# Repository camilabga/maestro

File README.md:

# Repository made to support the project Maestro
 
## Introduction
The project consists in a system designed to teach and correct the movement of a blind student that aims to learn a movement. With a OpenCV algorithm and a wearable, we made it possible to these students have a better perception to wheather they are making the gesture correctly or not.

The correction of the movement is passed to the user with an haptic feedback in real time while he/she is executing the gesture.

This work proposes a human gesture evaluation with visual detection and haptic feedback as an additional tool. The purpose is to utilize gesture monitoring with a visual detection alongside markers to execute a gesture following and then, send a haptic feedback to the user.

The project evolved to a different direction. To filter the gesture, we use a machine learning algorithm. At first, a SOM neural network was tested, but then the problem fitted better with a network called [GWR](https://www.sciencedirect.com/science/article/pii/S0893608002000783).

## Installing the requisites
* OpenCV 3.4.x [Installation Guide](https://docs.opencv.org/master/d7/d9f/tutorial_linux_install.html)
* ArUco 3.0.10 [Installation Guide](http://maztories.blogspot.com/2013/07/installing-aruco-augmented-reality.html)

This project was initially executed on a Linux environment with the distribution Ubuntu 16.04. The OpenCV version was 3.4.1 and the ArUco version was 3.0.10. The machine had an Intel Core i5 7th generation and 8GB of RAM Memory.

## Configuring the Wearable

1. Regular motors activation
2. Alternated motors activation

### Regular motors activation
to do

### Alternated motors activation
to do 

## Running the code
The main code is in the ../structure directory. To execute it you must, first choose the mode of execution by editing the **main.cpp** file and the project that contains the NN algorithm (GWR).

It has 4 modes:
1. Recording a new Gesture
2. Running the data through the GWR
3. Running the correction algorithm without the Wearable
4. Running the correction algorithm with the Wearable

### Recording a new Gesture
Open the file **main.cpp** and edit it to look like this:

```c++
Vision vision(argc, argv);
    Trajectory trajectory("../data/square.csv");
    
    trajectory.unnormalize(Point(FRAME_WIDTH/2, FRAME_HEIGHT/2));

    trajectory.saveMovement("../data/new_movement.csv");
    vision.record("../../Videos/random_test.avi");

    while(1){
        vision.calculateTagCenter();
        if (vision.isTargetOn()) {
            trajectory.savePoint(vision.getCenter());
            vision.saveVideo();
        }

        vision.show();
        vision.saveVideo();
    }

    trajectory.endSaving();
```

### Running the data through the GWR
to do

### Running the correction algorithm without the Wearable
Open the file **main.cpp** and edit it to look like this:

```c++
    Vision vision(argc, argv);
    Trajectory trajectory("../data/square.csv");
    trajectory.unnormalize(Point(FRAME_WIDTH/2, FRAME_HEIGHT/2));
    trajectory.saveMovement("../data/random_test.csv");

    while(1){
        vision.calculateTagCenter();
        vision.drawTrajectory(trajectory, trajectory.getCurrentPointId());
        if (vision.isTargetOn()) {
            trajectory.setNextPoint0(vision.getCenter());
            vision.drawError(vision.getCenter(), trajectory.getCurrentPoint());
            trajectory.savePoint(vision.getCenter());
        }

        vision.show();
    }

    trajectory.endSaving();
```

### Running the correction algorithm with the Wearable
Open the file **main.cpp** and edit it to look like this:

```c++
    Vision vision(argc, argv);
    Weareable weareable;
    Trajectory trajectory("../data/square.csv");

    trajectory.unnormalize(Point(FRAME_WIDTH/2, FRAME_HEIGHT/2));
    trajectory.saveMovement("../data/random_test.csv");

    weareable.setIP((char*)"10.6.4.107");
    weareable.start();

    while(1){
        vision.calculateTagCenter();
        vision.drawTrajectory(trajectory, trajectory.getCurrentPointId());
        if (vision.isTargetOn()) {
            trajectory.setNextPoint0(vision.getCenter());
            vision.drawError(vision.getCenter(), trajectory.getCurrentPoint());

            weareable.send(trajectory.getError(vision.getCenter()));

            trajectory.savePoint(vision.getCenter());
        }

        vision.show();
    }

    trajectory.endSaving();
```

## Article(s) Published
### Human Gesture Evaluation with Visual Detection and Haptic Feedback
**Abstract:** Learning a gesture pertains to learning a expression of motion by a human, involving the hands, arms, face, head, and/or body. In this work, we propose to employ haptic feedback as an additional tool in the gesture following/evaluation loop. Accordingly, the user wears a haptic wearable device in the form of a bracelet which vibrates according to the trajectory error. Our research hypothesis is then to investigate whether such haptic device aids the user in correcting his movement in relation to the prerecorded trajectory.

**Acess in:** https://dl.acm.org/citation.cfm?id=3243104

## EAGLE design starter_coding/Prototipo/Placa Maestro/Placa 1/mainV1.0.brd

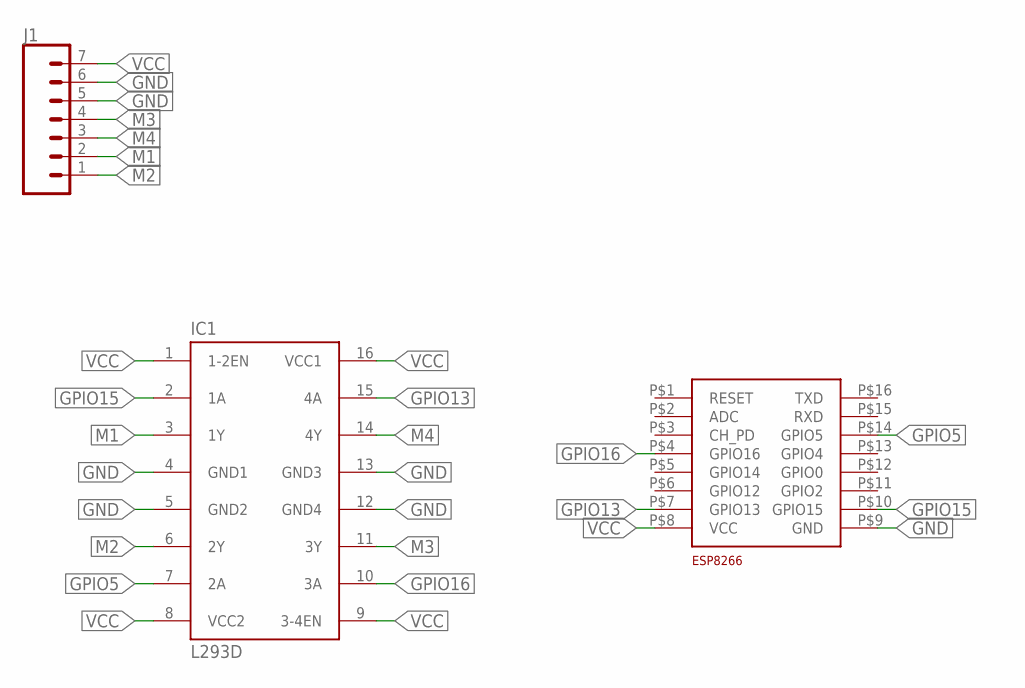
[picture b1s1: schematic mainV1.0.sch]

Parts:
IC1: L293D; DIL16
J1: CONN_07; 1X07
U$1: ESP_THIAGO

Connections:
GND: IC1.4 (GND1), IC1.5 (GND2), IC1.12 (GND4), IC1.13 (GND3), J1.5, J1.6, U$1.P$9 (GND)
GPIO5: IC1.7 (2A), U$1.P$14 (GPIO5)
GPIO13: IC1.15 (4A), U$1.P$7 (GPIO13)
GPIO15: IC1.2 (1A), U$1.P$10 (GPIO15)
GPIO16: IC1.10 (3A), U$1.P$4 (GPIO16)
M1: IC1.3 (1Y), J1.2
M2: IC1.6 (2Y), J1.1
M3: IC1.11 (3Y), J1.4
M4: IC1.14 (4Y), J1.3
VCC: IC1.1 (1-2EN), IC1.9 (3-4EN), IC1.16 (VCC1), J1.7, U$1.P$8 (VCC)

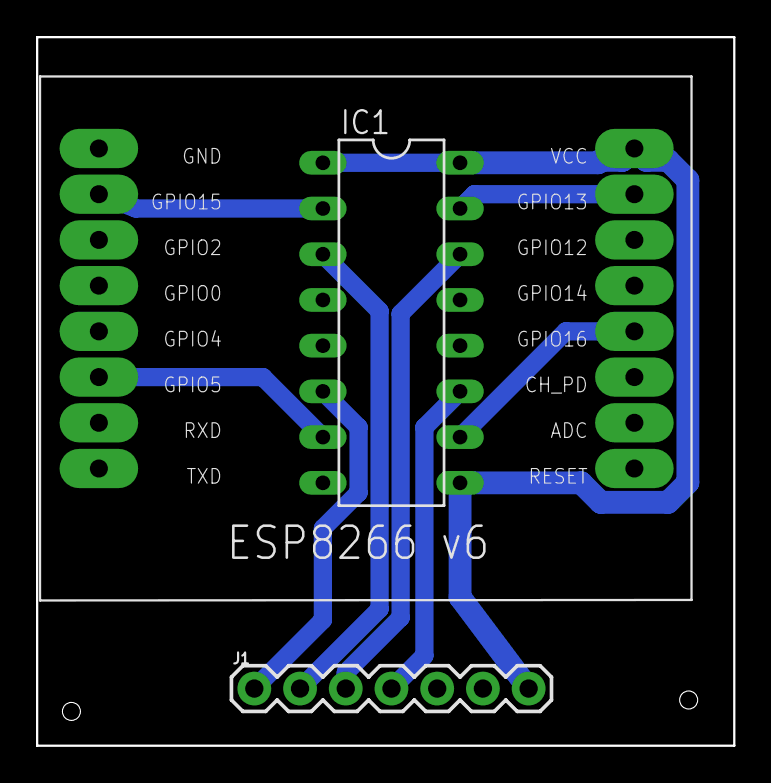
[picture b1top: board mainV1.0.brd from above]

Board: 2 copper layers, 38.7 x 39.4 mm, 3 parts (0 on the bottom side), 10 nets.

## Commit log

2018-08-16 repository description
2018-08-16 getting files from old repository
2018-08-16 data files from old tests
2018-08-16 starter codes - base to structurer
2018-08-16 repository description atualization
2018-08-16 run test - new enviroment
2018-08-20 simple updates
2018-09-01 no more warnings
2018-09-06 description att
2019-04-11 Starting python visualization
2019-04-13 Tentando ler de arquivo
2019-04-16 stable changes
2019-04-21 adding test files
2019-04-21 few changes
2019-05-23 Trying to exclude .vscode + lots of work
2019-05-23 adding .vscode to remove it
2019-06-03 porting camera.py to cpp
2019-06-03 circle tracking not working
2019-06-05 circle tracking kinda working
2019-06-05 circle tracking working
2019-06-05 circle tracking working and on Vision.cpp
2019-06-06 Qt files added
2019-06-11 Untracking unused Qt files
2019-06-19 Working on Circle Tracking
2019-07-23 Circle tracker Angelo V1.0 + Angelo PDI stuff
2019-07-26 Oi esse commit foi muuuuito legal. Ele vai ser para testar o Qt no computer de pudimi. FIM ;-)
2019-07-26 Cleaning user interface files
2019-07-26 Cleaning stash files
2019-07-26 updated Vision.h
2019-08-19 Audio feedback improvement
2019-08-20 Audio generator header added
2019-08-20 backup
2019-08-23 audio feedback for point change implemented
2019-08-28 final tweaking before 30/08/19
2019-08-29 Audio Feedback v1.0 done, commiting changes before trying to fix image size
2019-09-03 Test-ready code with psmove tracker, .csv file sorted, metronome, tap sound and audible feedback. Also adding fisrt attempt to increase tracking confiabiity
2019-09-04 Adding metronome_click.wav + README.md with instructions for running the Qt project anywhere
2019-09-04 Update README.md for running the Qt project
2019-09-10 Interface button layout changed
2019-09-10 Interface updated + data files refactor
2019-09-10 checkout update
2019-09-10 Interface updated + plot added
2019-09-13 Major interface updated + logic refined
2019-09-24 Interface gráfica atualizada, Vision.cpp adaptada para batuta
2019-09-24 Interface atualizada, novos sons adicionados
2019-09-24 Return Commit
2019-09-26 Função de Ativar/Desativar Pulseira adicionada
2019-10-10 Tornando o programa estável
2019-10-24 Saving changes before refactoring Trajectory display
2019-10-24 Trajectory display fix + start backround img
2019-11-13 Audio description added + stable version
2019-11-13 code update
2019-11-16 Maestro Software v0.1

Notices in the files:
parts and their libraries:
SparkFun-Connectors: Licensing: Creative Commons ShareAlike 4.0 International - https://creativecommons.org/licenses/by-sa/4.0
